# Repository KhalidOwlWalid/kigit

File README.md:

<div align="center">

# kigit

### Visual diffs for KiCad PCBs and schematics, straight from git.

</div>

**kigit** utilizes the use of git logs in order to allow user to perform diffs between their pcb and schematic files. It provides a proper visual feedback which helps in identifying changes made per commit basis. Hence where its name came from, combination of Ki from KiCAD and git itself (kigit!). 

What it can do:

- Compare your PCB between any two commits, visually
- Show what changed on your symbols and their fields
- Show your buses and where they're routed
- Works without git too: just point it at two folders

Have a look at the demo below to get a feel for it.

## Demonstration

https://github.com/user-attachments/assets/f906914c-ffff-49df-a43d-28ec8a625058

Full documentation can be found here: https://khalidowlwalid.github.io/kigit/

### PCB diff

### Schematic diff

---

## What kigit is not

kigit is an application that was built out of frustration of not having a kind of proper "git diff" for kicad for myself. Having came from a software background and being used to utilizing git versioning for all of my projects, not being able to do the same in a manner that I can compare my pcb and schematic visually between different commits without having to diff the .kicad_pcb and .kicad_sch files really frustates me. I am aware of the fact that there are other resources out there as shown below:

- [KiRI](https://github.com/leoheck/kiri)
- [KiCAD-Prism](https://krishna-swaroop.github.io/KiCAD-Prism/get-started/what-is-prism/)
- [KiHub](https://kihub.dev/)

They all have their pros and cons. KiRI is what got me excited about diffing schematics in the first place, and honestly, huge respect to the folks behind it. It's a great community effort, built well before AI was a thing.

The other two I didn't even know existed when I started. Funnily enough, not even Claude mentioned them when I first went looking for alternatives.

KiCAD-Prism and KiHub are in the same space and cover a lot of what kigit does. KiCAD-Prism is a whole package: free, open source, and the demos look amazing. But it needs a fair bit of Docker setup, which can be a turn-off if you're a hobbyist who just wants to design boards. KiHub needs a login, doesn't run offline, and is really aimed at teams collaborating (PR reviews and that kind of thing).

Me? I'm a hobbyist who only recently got into PCB design and out of this frustration, I figured: why not just make my own PCB diff that does just enough for what I need? Nothing fancy. It runs locally, it's a simple download, and it works on Linux and Windows. (Sorry macOS folks, I'm broke and not about to buy a Mac just for this.)

So, what kigit is **not** is a collaboration tool. It's for people who wants a simple app they can download, or open in a browser, to check what changed in their PCB designs. That's it.

## License

kigit is free and open source under the [MIT License](LICENSE): use it, fork it and change it, in public or private projects, with no need to open-source your own work. Third-party licenses are in [THIRD_PARTY_NOTICES.md](THIRD_PARTY_NOTICES.md).

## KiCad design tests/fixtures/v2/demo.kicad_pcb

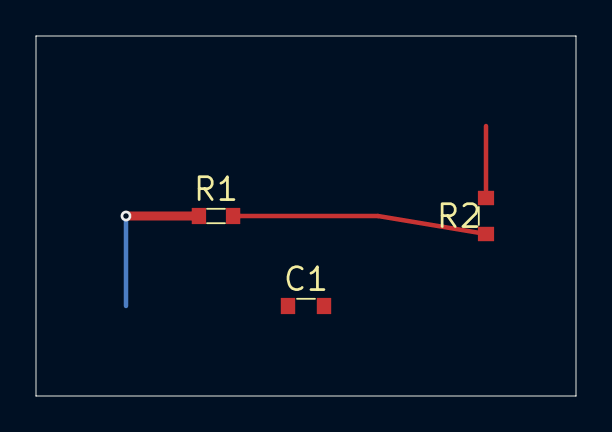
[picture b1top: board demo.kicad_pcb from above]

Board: 2 copper layers, 30.0 x 20.0 mm, 3 parts (0 on the bottom side), 3 nets.

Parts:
C1: 1k; R
R1, R2: 1k; R

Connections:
GND: C1.2, R2.2
SIG: R1.2, R2.1
VCC: C1.1, R1.1
